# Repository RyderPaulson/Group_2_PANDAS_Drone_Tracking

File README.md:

# PANDAS: Point-based Autonomous Networked Drone Aiming System
Siman Zhang | James Lewis | Shree Singhal | Ryder Paulson | Patrick Donnelly | Burke Havranek

A laser-based tracking and charging system designed to enable continuous in-flight drone operation.

## Installation Guide

1. Clone the repository.

```
git clone https://github.com/RyderPaulson/Group_2_PANDAS_Drone_Tracking
cd Group_2_PANDAS_Drone_Tracking
```

2. Create a v3.12.11 Python virtual environment. Conda is recommended but not required.
3. Install CUDA.

```
# check if cuda is installed
nvcc --version
```

If it is not installed, install the appropriate CUDA 12.6 version for your system from [here](https://developer.nvidia.com/cuda-12-6-0-download-archive). Set the CUDA_HOME environmental variable to your CUDA instillation.

4. Clone and install CoTracker3.

```
git clone https://github.com/facebookresearch/co-tracker
cd co-tracker
pip install -e .
pip install matplotlib flow_vis tqdm tensorboard
mkdir weights
cd weights
# download the online (multi window) model
wget https://huggingface.co/facebook/cotracker3/resolve/main/scaled_online.pth
# download the online (sliding window) model
wget https://huggingface.co/facebook/cotracker3/resolve/main/baseline_online.pth
cd ..
cd ..
```

5. Clone and install GroundingDINO.

```
git clone https://github.com/IDEA-Research/GroundingDINO.git
cd GroundingDINO
```

6. Implement [this change](https://github.com/IDEA-Research/GroundingDINO/pull/415) from GroundingDINO
7. Finish the install of GroundingDINO

```
pip install -e .
mkdir weights
cd weights
wget -q https://github.com/IDEA-Research/GroundingDINO/releases/download/v0.1.0-alpha/groundingdino_swint_ogc.pth
```

6. Download the tiny weights from our Google Drive [groundingdino_swint_ogc](https://drive.google.com/file/d/1JuvtEhrE4oPX_5h5dwdAwMy35T0FAJLR/view?usp=drive_link) into the weights folder.
7. Uninstall PyTorch and bundled packages.

```
pip uninstall torch torchvision
```

8. Navigate to [PyTorch's website](https://pytorch.org/) and install get the correct command for installing PyTorch with CUDA 12.6 on your system.
9. Install remaining required Python packages. 

TODO

## Requirements
### Core
1. PyTorch > 2.0.0
2. CV2 Latest
3. CUDA 12.6
4. [CoTracker3](https://github.com/facebookresearch/co-tracker)
5. [GroundingDINO](https://github.com/IDEA-Research/GroundingDINO)

### Jetson Specific
TODO Check on Jetson board for specific requirements.

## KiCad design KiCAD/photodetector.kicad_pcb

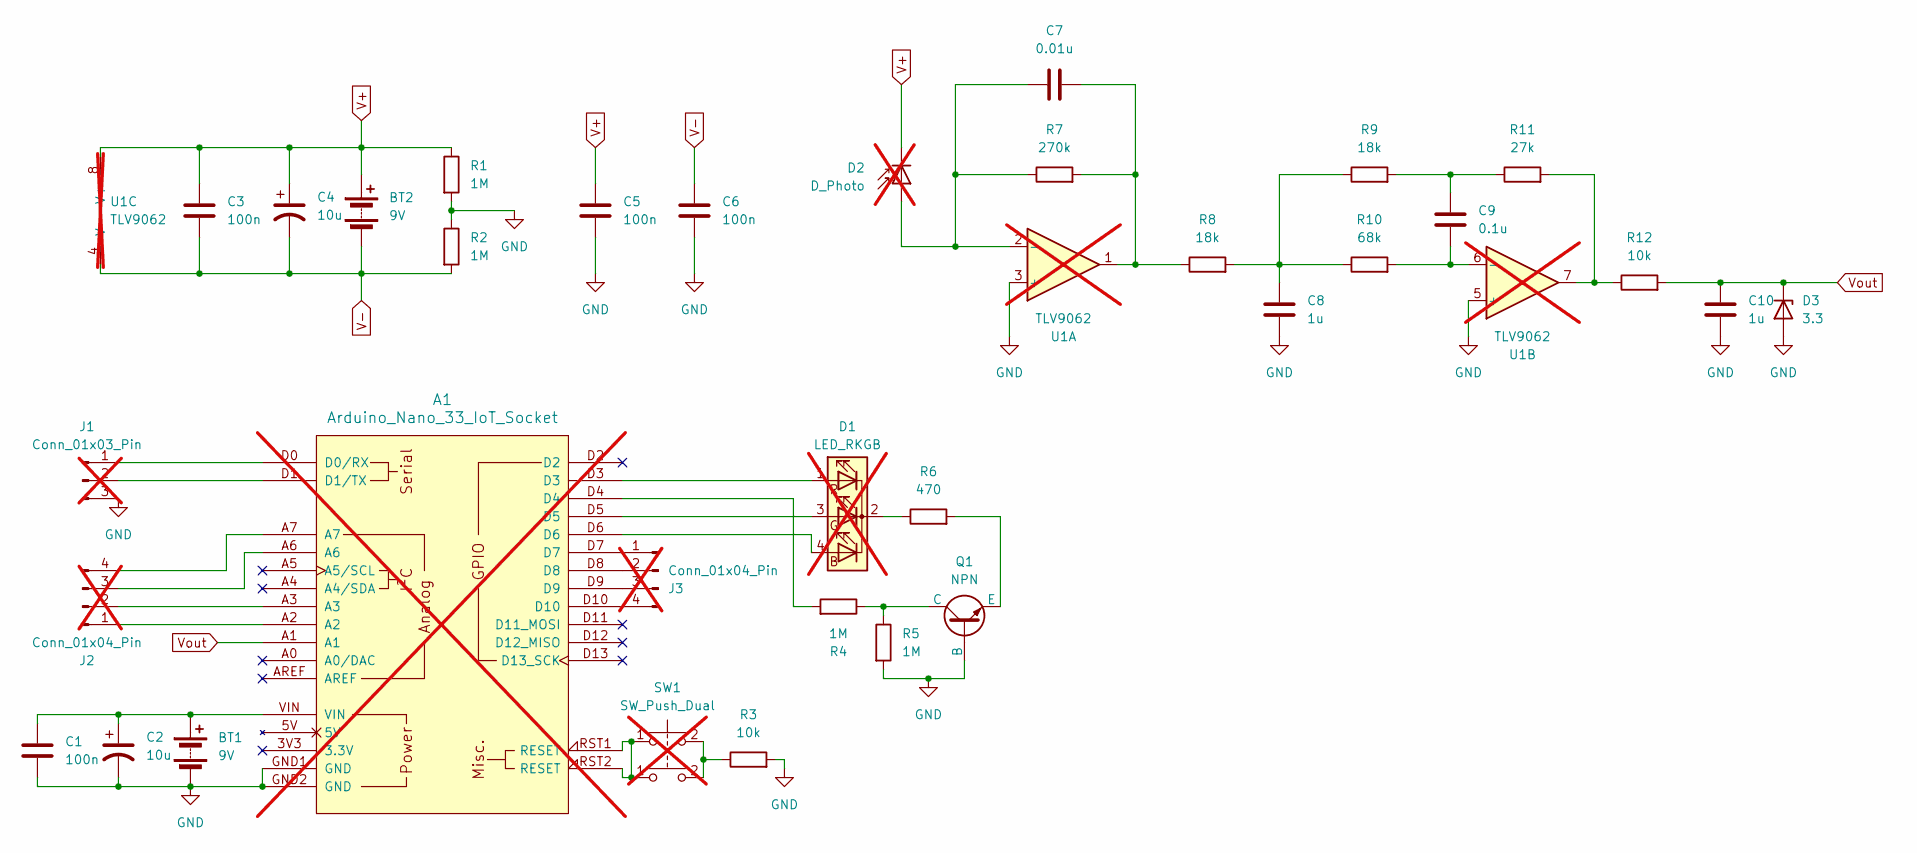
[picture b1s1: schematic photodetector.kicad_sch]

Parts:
A1: Arduino_Nano_33_IoT_Socket; not fitted
BT1, BT2: 9V; BatteryHolder_MPD_BA9VPC_1xPP3
C1, C3, C5, C6: 100n; C_0402_1005Metric
C2, C4: 10u; CP_Elec_4x5.4
C7: 0.01u; C_0402_1005Metric
C8, C10: 1u; C_0402_1005Metric
C9: 0.1u; C_0402_1005Metric
D1: LED_RKGB; LED_D5.0mm-4_RGB_Wide_Pins; not fitted
D2: D_Photo; LED_D5.0mm_FlatTop; not fitted
D3: 3.3; D_0402_1005Metric
J1: Conn_01x03_Pin; FanPinHeader_1x03_P2.54mm_Vertical; not fitted
J2, J3: Conn_01x04_Pin; FanPinHeader_1x04_P2.54mm_Vertical; not fitted
Q1: NPN; SOT-23
R1, R2, R4, R5: 1M; R_0402_1005Metric
R3, R12: 10k; R_0402_1005Metric
R6: 470; R_0402_1005Metric
R7: 270k; R_0402_1005Metric
R8, R9: 18k; R_0402_1005Metric
R10: 68k; R_0402_1005Metric
R11: 27k; R_0402_1005Metric
SW1: SW_Push_Dual; SW_PUSH_6mm; not fitted
U1: TLV9062; SOIC-8_3.9x4.9mm_P1.27mm; not fitted

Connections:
GND: A1.GND1 (GND), A1.GND2 (GND), BT1.2 (-), C1.2, C2.2, C5.2, C6.2, C8.2, C10.2, D3.2 (A), J1.3, Q1.2 (B), R1.2, R2.1, R3.2, R5.2, U1.3 (+), U1.5 (+)
unnamed: A1.D0 (D0/RX), J1.1
unnamed: A1.D1 (D1/TX), J1.2
unnamed: A1.D4, R4.2
unnamed: A1.RST1 (RESET), A1.RST2 (RESET), SW1.1
unnamed: A1.VIN, BT1.1 (+), C1.1, C2.1
unnamed: C7.2, R7.2, R8.1, U1.1
unnamed: C8.1, R8.2, R9.1, R10.1
unnamed: C9.1, R9.2, R11.1
unnamed: A1.D6, D1.4 (BA)
unnamed: A1.D5, D1.3 (GA)
unnamed: D1.2 (K), R6.1
unnamed: A1.D3, D1.1 (RA)
unnamed: C7.1, D2.2 (A), R7.1, U1.2 (-)
unnamed: A1.A2, J2.1
unnamed: A1.A3, J2.2
unnamed: A1.A6, J2.3
unnamed: A1.A7, J2.4
unnamed: A1.D7, J3.1
unnamed: A1.D8, J3.2
unnamed: A1.D9, J3.3
unnamed: A1.D10, J3.4
unnamed: Q1.1 (C), R4.1, R5.1
unnamed: Q1.3 (E), R6.2
unnamed: R3.1, SW1.2
unnamed: R11.2, R12.1, U1.7
unnamed: C9.2, R10.2, U1.6 (-)
V+: BT2.1 (+), C3.1, C4.1, C5.1, D2.1 (K), R1.1, U1.8 (V+)
V-: BT2.2 (-), C3.2, C4.2, C6.1, R2.2, U1.4 (V-)
Vout: A1.A1, C10.1, D3.1 (K), R12.2

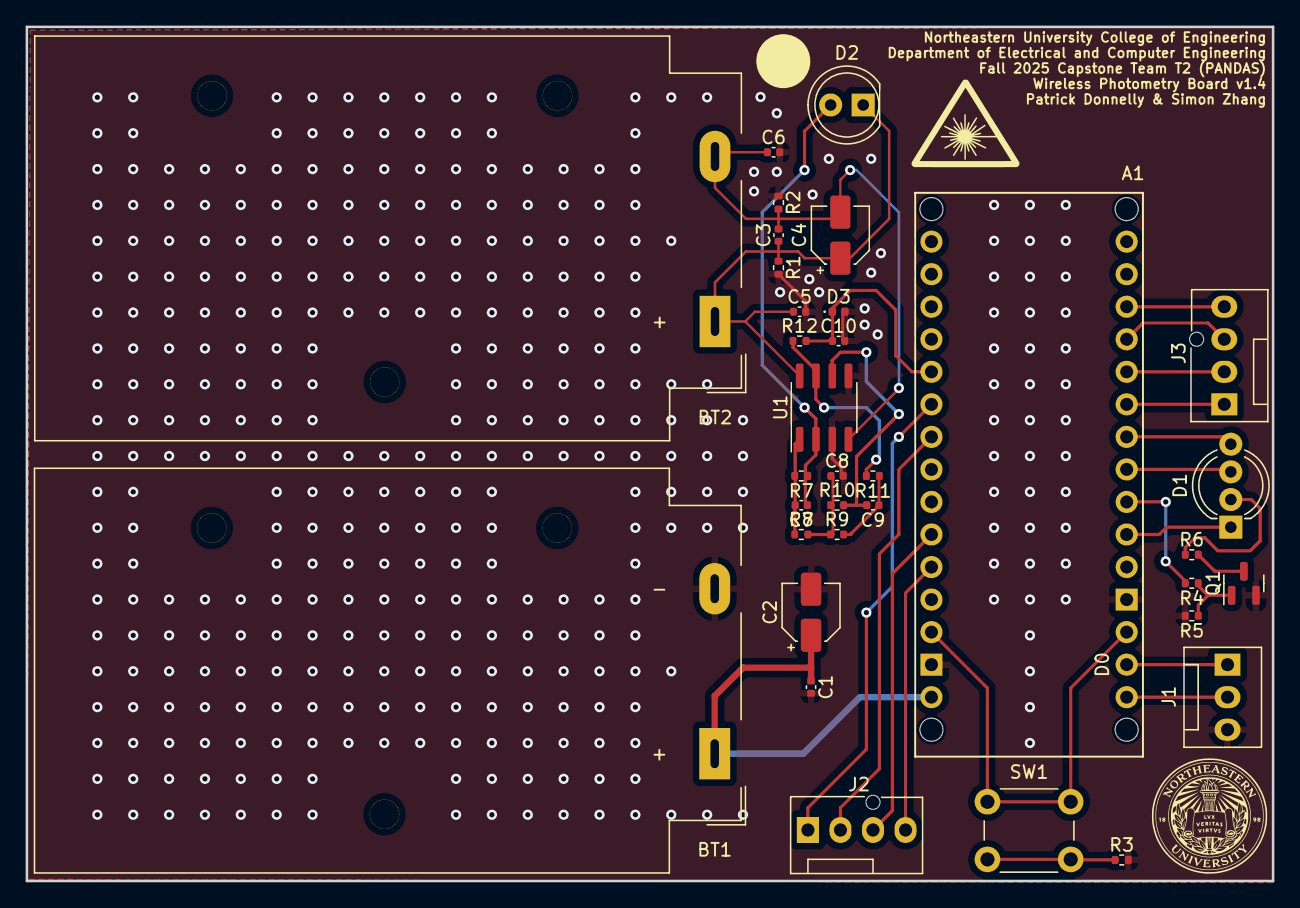
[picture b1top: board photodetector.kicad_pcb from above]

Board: 2 copper layers, 97.3 x 66.7 mm, 34 parts (0 on the bottom side), 30 nets.

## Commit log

2025-09-07 Initial commit - not currently working. cotracker_matlab_interface.py
2025-09-07 Added gitignore.
2025-09-07 Updated gitignore to exclude JetBrains IDE folder.
2025-09-08 Removed redundant IO code and changed to pass through image input to output for simulation testing.
2025-09-08 Refactored API connecting Co-Tracker and MATLAB and removed code that no-longer matches the design intent.
2025-09-10 Formatted using Black.
2025-09-10 Modified to be class based rather than function based with global variable. Also, added argument validation to initialization function.
2025-09-10 Replaced annotated video viewer with terminator because currently the system just passes through the video so it's redundant.
2025-09-15 Added code that I used to set a tracking point on a specific pixel.
2025-09-17 Modified CoTrackerCORE to process sliding window and fixed model erroring on first call. Current Issue: CoTracker returning None for predictions.
2025-09-19 Removed apple test and added Bishoy's point selection script (not currently workring).
2025-09-19 Fixed CoTracker not running.
2025-09-20 Fixed CoTracker not working with query points.
2025-09-28 Added GroundedDINO Prototype.
2025-09-28 Refactored simulation tools to be in their own directory.
2025-09-30 Moved helper functions from test files to its own file.
2025-09-30 Added Simulink generated files to gitignore
2025-09-30 Got GroundedDINO working on a video.
2025-10-02 Added __pycache__
2025-10-02 Moved to simulation folder
2025-10-02 Refactored to represent that there's other components other than cotracker.
2025-10-02 Implemented GroundedDINO and masking algorithms.
2025-10-02 Deleted requirements because they don't work anyway.
2025-10-02 Changed README to focus on the requirements. Removed outdated installation instructions.
2025-10-02 Added dependant media.
2025-10-02 First Draft of Turret Controls System
    Open with STM32CubeIDE. So far this code just allows you to set the servo to an angle using the nucleo.
2025-10-06 i2c master test
2025-10-07 Main file to run CoTracker from.
2025-10-07 Added utilities to display and write live video.
2025-10-07 Implemented reset system for CoTracker.
2025-10-07 Moved normalize_np_img to utils.py.
2025-10-07 Renamed GroundedDINO class to GroundingDINO.
2025-10-07 Modified to work with new reset function.
2025-10-08 main c file for turret controls
2025-10-08 added Jetson PWM test
2025-10-19 Finished implementation of main loop.
2025-10-19 Added test suite for main loop.
2025-10-22 Moved test files to separate directory.
2025-10-22 Moved some IO functionality to a utility class.
2025-10-22 Created launch scripts and added argument parsing to main.
2025-10-25 Created bridge file for integration with MATLAB.
2025-10-25 Added parameter for image size.
2025-10-25 Modified target_size to be a ration of max_size rather than a hard coded value.
2025-10-25 Simulation is able to pass through the image but not annotate it.
2025-10-25 Added backup MATLAB files.
2025-10-25 Modified GroundingDINO to use tiny model.
2025-10-25 Removed meta logo from simulink model.
2025-10-30 Ignore vision library and temp folder.
2025-10-31 motorControl file used for demo 10/31
2025-11-01 Works with exponential decay and other design changes
2025-11-02 Pushed firmware
2025-11-02 Recursive algo
2025-11-03 control 2 servos finicky
2025-11-05 debug
2025-11-06 Removed unused package imports.
2025-11-06 Normalize and center the coordinate send to motor controller (checked comparing values to unadjusted printout but not verified on board).
2025-11-06 GroundingDINO now selects highest score prediction instead of first prediction.
2025-11-07 Fixed pwm call bug in trackCoords. Scaled coordinates to -1,1
2025-11-10 Added try except for motorControl import because it relies on Jetson.
2025-11-12 Made the target color an argument.
2025-11-12 Grounding DINO returns no prediction if confidence is under 0.5.
2025-11-13 Ozz attempts + inprogress motor changes
2025-11-13 Trying to get a PD working
2025-11-14 Removed unused local point selector
2025-11-14 Cotracker only sends coordinate to motor if it's different then the previous prediction.
2025-11-14 Moved main loop into a function so that GD will continually try to find a target with sufficient confidence instead of just tracking 0,0.
2025-11-14 Moved some code out of the tracking loop for efficiency purposes.
2025-11-14 100ms steps, scale factor 13 motorControl
2025-11-19 Continuous tracking attempt. Bugs when trying to restart PWM after losing the point and reacquiring
2025-11-19 Added keyboard interrupt
2025-11-19 Continuous tracking + shutdown event handler + separate x and y scale factors
2025-11-20 Added reset, tuning parameters
2025-11-21 Updated README with installation instructions.
2025-11-21 Added GroundDINO change request for newer versions.
